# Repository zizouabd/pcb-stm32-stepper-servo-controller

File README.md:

# 🚀 Contrôleur STM32 - 2x Moteurs Pas-à-Pas (A4988) & 4x Servomoteurs

Ce dépôt contient la conception matérielle complète (schématique et PCB 2 couches $100\text{ mm} \times 100\text{ mm}$) d'une carte de contrôle embarquée pour la robotique et l'automatisme. Elle est pilotée par une **STM32 Black Pill** et alimentée par une batterie **LiPo 3S (12V)**.

---

## 📸 Aperçu du Projet

### 1. Schéma Électrique

### 2. Routage PCB (Vue 2D)

### 3. Rendu 3D de la Carte

---

## ⚡ Architecture d'Alimentation : La stratégie des "Deux Bucks"

La carte accepte une tension d'entrée principale $12\text{ V}$ via un connecteur **XT60**. Pour garantir une stabilité maximale et isoler les bruits électromécaniques, nous avons fait le choix d'intégrer **deux convertisseurs Buck (DC-DC) distincts** :

### 1. Buck 3.3V (Logique & Microcontrôleur)
* **Rôle :** Alimentation stable du STM32 (broche `VDD`) et des entrées logiques des drivers A4988.
* **Intérêt :** Consommation faible et constante. L'isolation de ce rail protège le processeur contre les chutes de tension (*brownouts*).

### 2. Buck 5V (Puissance Servomoteurs)
* **Rôle :** Alimentation directe des 4 servomoteurs (`J5` à `J8`) et du rail `VIN` de secours.
* **Intérêt :** Absorbe les forts appels de courant et le bruit inductif (*Back-EMF*) générés par les moteurs des servos sans impacter la logique numérique du STM32.

---

## 🔋 Rôle et Placement des Condensateurs de Filtrage ($220\text{ µF}$)

Pour assurer la longévité des composants et la stabilité des tensions, des condensateurs électrolytiques de **$220\text{ µF}$** ont été intégrés aux emplacements stratégiques de la carte :

### 1. Condensateurs sur la ligne `VMOT` des A4988 ($220\text{ µF}$)
Placés au plus près de la broche d'alimentation haute tension (`VMOT`) de chaque driver pas-à-pas :
* **Protection contre les surtensions inductives (Back-EMF) :** Les bobines des moteurs pas-à-pas génèrent de violents pics de tension en retour lors des commutations rapides ou du freinage. Sans ces condensateurs de $220\text{ µF}$, ces transitoires peuvent dépasser la tension maximale tolérée par le A4988 ($35\text{ V}$) et détruire instantanément le driver.
* **Réservoir d'énergie local :** Ils fournissent l'énergie instantanée nécessaire au hachage PWM du courant dans les phases des moteurs, évitant que les pics de courant ne se propagent sur toute la ligne $12\text{ V}$.

### 2. Condensateur en sortie du Buck 5V ($220\text{ µF}$)
Placé immédiatement en sortie du convertisseur $5\text{ V}$ alimentant les servomoteurs :
* **Absorption des pics de démarrage (Inrush Current) :** Un servomoteur peut appeler plusieurs ampères pendant quelques millisecondes lorsqu'il démarre ou change brutalement de sens. Ce condensateur de $220\text{ µF}$ sert de réservoir d'énergie immédiat pour lisser ces appels de courant et éviter l'écroulement de la ligne $5\text{ V}$.
* **Filtrage de l'ondulation (Ripple) :** Il réduit le bruit haute fréquence issu du hachage interne du Buck $5\text{ V}$, garantissant un signal propre pour les servos et l'électronique annexe.

---

## 📐 Création des Empreintes Personnalisées (Custom Footprints)

Afin d'assurer un assemblage parfait et de respecter les dimensions compactes de la carte ($100\text{ mm} \times 100\text{ mm}$), plusieurs empreintes spécifiques ont été créées sur mesure dans une bibliothèque dédiée du projet (`.pretty`) :

* **Modules Buck DC-DC (`buck3.3V1` & `buck5V1`) :** Les modules abaisseurs génériques ne possédant pas de standard de perçage universel, leurs empreintes ont été modélisées manuellement (espacement exact des broches `IN+`, `IN-`, `OUT+`, `OUT-` et dimensions hors-tout) pour s'intégrer directement comme cartes filles.
* **STM32 Black Pill (`Black_Pill_v3.1`) :** Empreinte personnalisée assurant le pitch standard de $2.54\text{ mm}$ entre les rangées de broches et l'intégration exacte du connecteur USB-C.

---

## 🛠️ Contraintes de Fabrication & Règles de Routage (DRC)

Le routage de la carte a été validé sous KiCad avec zéro erreur DRC selon les règles de fabrication industrielles standard :

| Paramètre | Valeur Minimale Validée |
| :--- | :--- |
| **Largeur des pistes de signal** (`STEP`, `DIR`, `SERVO`) | `0.3 mm`  |
| **Largeur des pistes de puissance** (`+5V`, `+12V`, Moteurs) | `0.8 mm` à `2.5 mm` |
| **Isolement entre pistes (Clearance)** | `0.3 mm` |
| **Distance cuivre au bord de carte (Edge.Cuts)** | `0.5 mm` |
| **Plan de masse** | Plan continu sur couche inférieure (`B.Cu`) |

---

## ⚠️ Note Importante : Configuration de la broche PA15 (SWD)

Sur cette carte, la broche **`PA15`** du STM32 est reliée au signal `MS2` du premier driver A4988.

* **Mode de programmation :** Par défaut, `PA15` est réservée à la fonction de débogage JTAG. Pour l'utiliser comme une broche d'entrée/sortie classique (GPIO), la programmation du STM32 **doit impérativement être effectuée en mode SWD (Serial Wire Debug)** via ST-Link (`SWDIO` sur PA13, `SWCLK` sur PA14).

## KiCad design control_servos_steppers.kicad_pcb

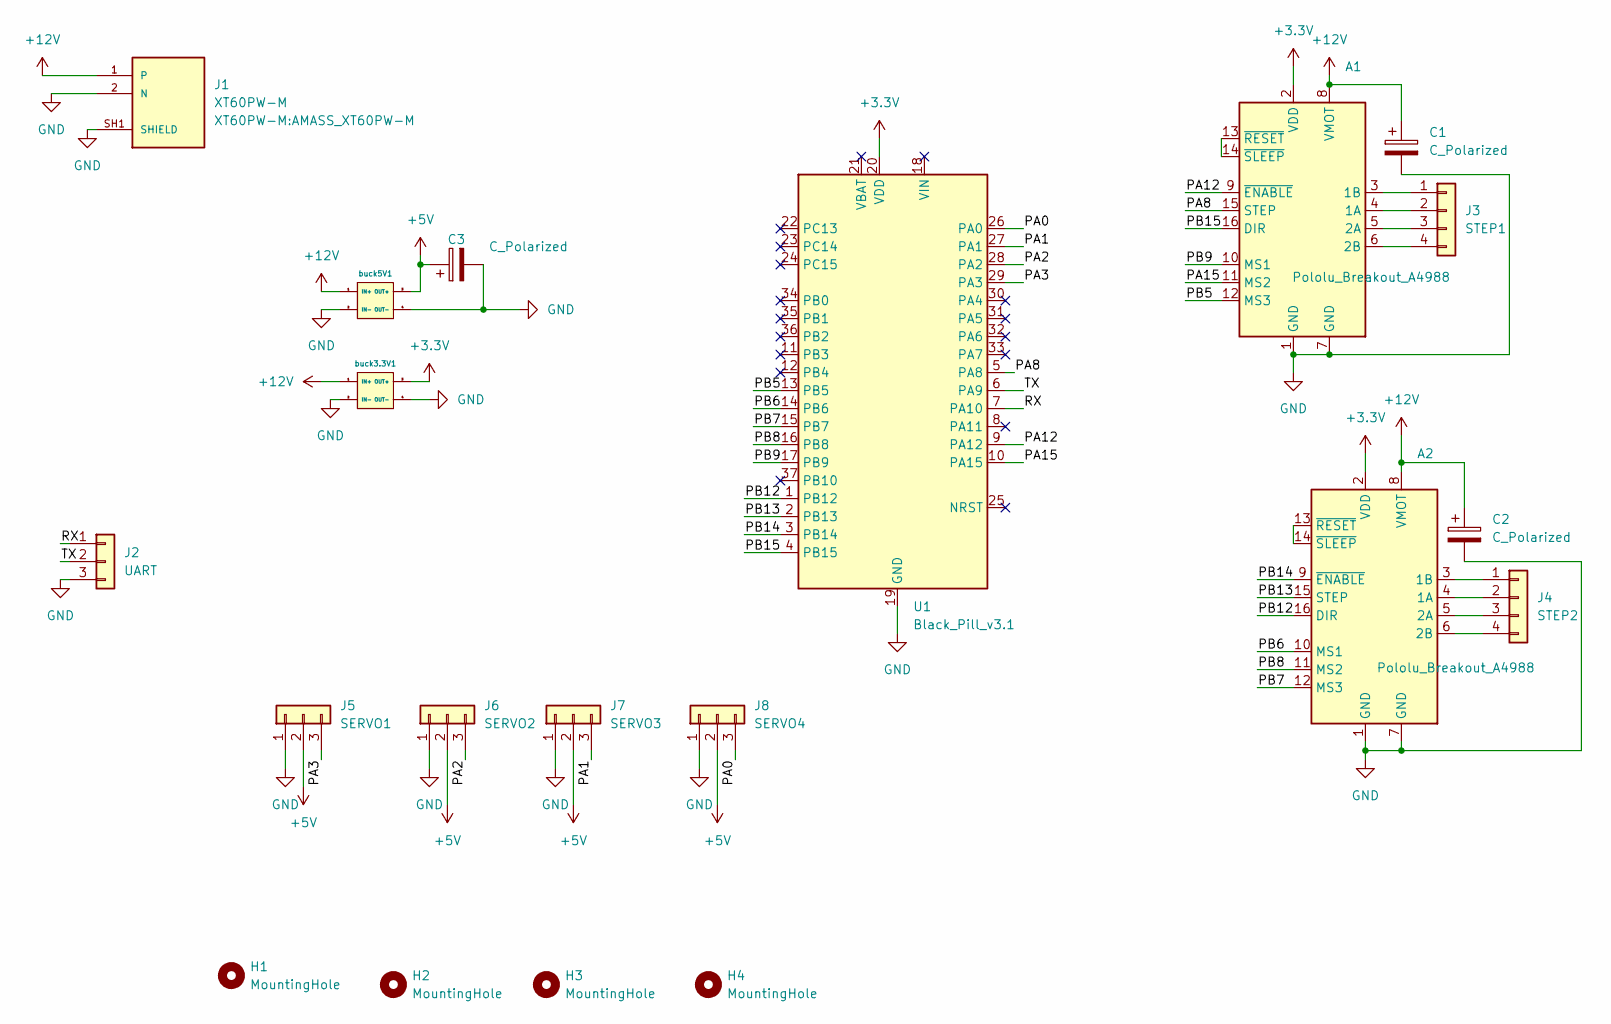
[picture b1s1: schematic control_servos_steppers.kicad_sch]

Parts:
A1, A2: Pololu_Breakout_A4988; Pololu_Breakout-16_15.2x20.3mm
C1, C2, C3: C_Polarized; CP_Radial_D8.0mm_P3.50mm
H1, H2, H3, H4: MountingHole; MountingHole_4.3mm_M4
J1: XT60PW-M; AMASS_XT60PW-M; PARTREV 1.2
J2: UART; PinHeader_1x03_P2.54mm_Vertical
J3: STEP1; PinHeader_1x04_P2.54mm_Vertical
J4: STEP2; PinHeader_1x04_P2.54mm_Vertical
J5: SERVO1; PinHeader_1x03_P2.54mm_Vertical
J6: SERVO2; PinHeader_1x03_P2.54mm_Vertical
J7: SERVO3; PinHeader_1x03_P2.54mm_Vertical
J8: SERVO4; PinHeader_1x03_P2.54mm_Vertical
U1: Black_Pill_v3.1
buck3.3V1, buck5V1: XL4015 buck module

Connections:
+3.3V: A1.2 (VDD), A2.2 (VDD), U1.20 (VDD), U1.38 (VDD), buck3.3V1.3 (OUT+)
+5V: C3.1, J5.2, J6.2, J7.2, J8.2, buck5V1.3 (OUT+)
+12V: A1.8 (VMOT), A2.8 (VMOT), C1.1, C2.1, J1.1, buck3.3V1.1 (IN+), buck5V1.1 (IN+)
/PA0: J8.3, U1.26 (PA0)
/PA1: J7.3, U1.27 (PA1)
/PA2: J6.3, U1.28 (PA2)
/PA3: J5.3, U1.29 (PA3)
/PA8: A1.15 (STEP), U1.5 (PA8)
/PA12: A1.9 (~ENABLE), U1.9 (PA12)
/PA15: A1.11 (MS2), U1.10 (PA15)
/PB5: A1.12 (MS3), U1.13 (PB5)
/PB6: A2.10 (MS1), U1.14 (PB6)
/PB7: A2.12 (MS3), U1.15 (PB7)
/PB8: A2.11 (MS2), U1.16 (PB8)
/PB9: A1.10 (MS1), U1.17 (PB9)
/PB12: A2.16 (DIR), U1.1 (PB12)
/PB13: A2.15 (STEP), U1.2 (PB13)
/PB14: A2.9 (~ENABLE), U1.3 (PB14)
/PB15: A1.16 (DIR), U1.4 (PB15)
/RX: J2.1, U1.7 (PA10)
/TX: J2.2, U1.6 (PA9)
GND: A1.1 (GND), A1.7 (GND), A2.1 (GND), A2.7 (GND), C1.2, C2.2, C3.2, J1.2 (N), J1.SH1 (SHIELD), J1.SH2 (SHIELD), J2.3, J5.1, J6.1, J7.1, J8.1, U1.19 (GND), U1.39 (GND), buck3.3V1.2 (IN-), buck3.3V1.4 (OUT-), buck5V1.2 (IN-), buck5V1.4 (OUT-)
unnamed: A1.4 (1A), J3.2
unnamed: A1.3 (1B), J3.1
unnamed: A1.5 (2A), J3.3
unnamed: A1.6 (2B), J3.4
unnamed: A1.13 (~RESET), A1.14 (~SLEEP)
unnamed: A2.4 (1A), J4.2
unnamed: A2.3 (1B), J4.1
unnamed: A2.5 (2A), J4.3
unnamed: A2.6 (2B), J4.4
unnamed: A2.13 (~RESET), A2.14 (~SLEEP)

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
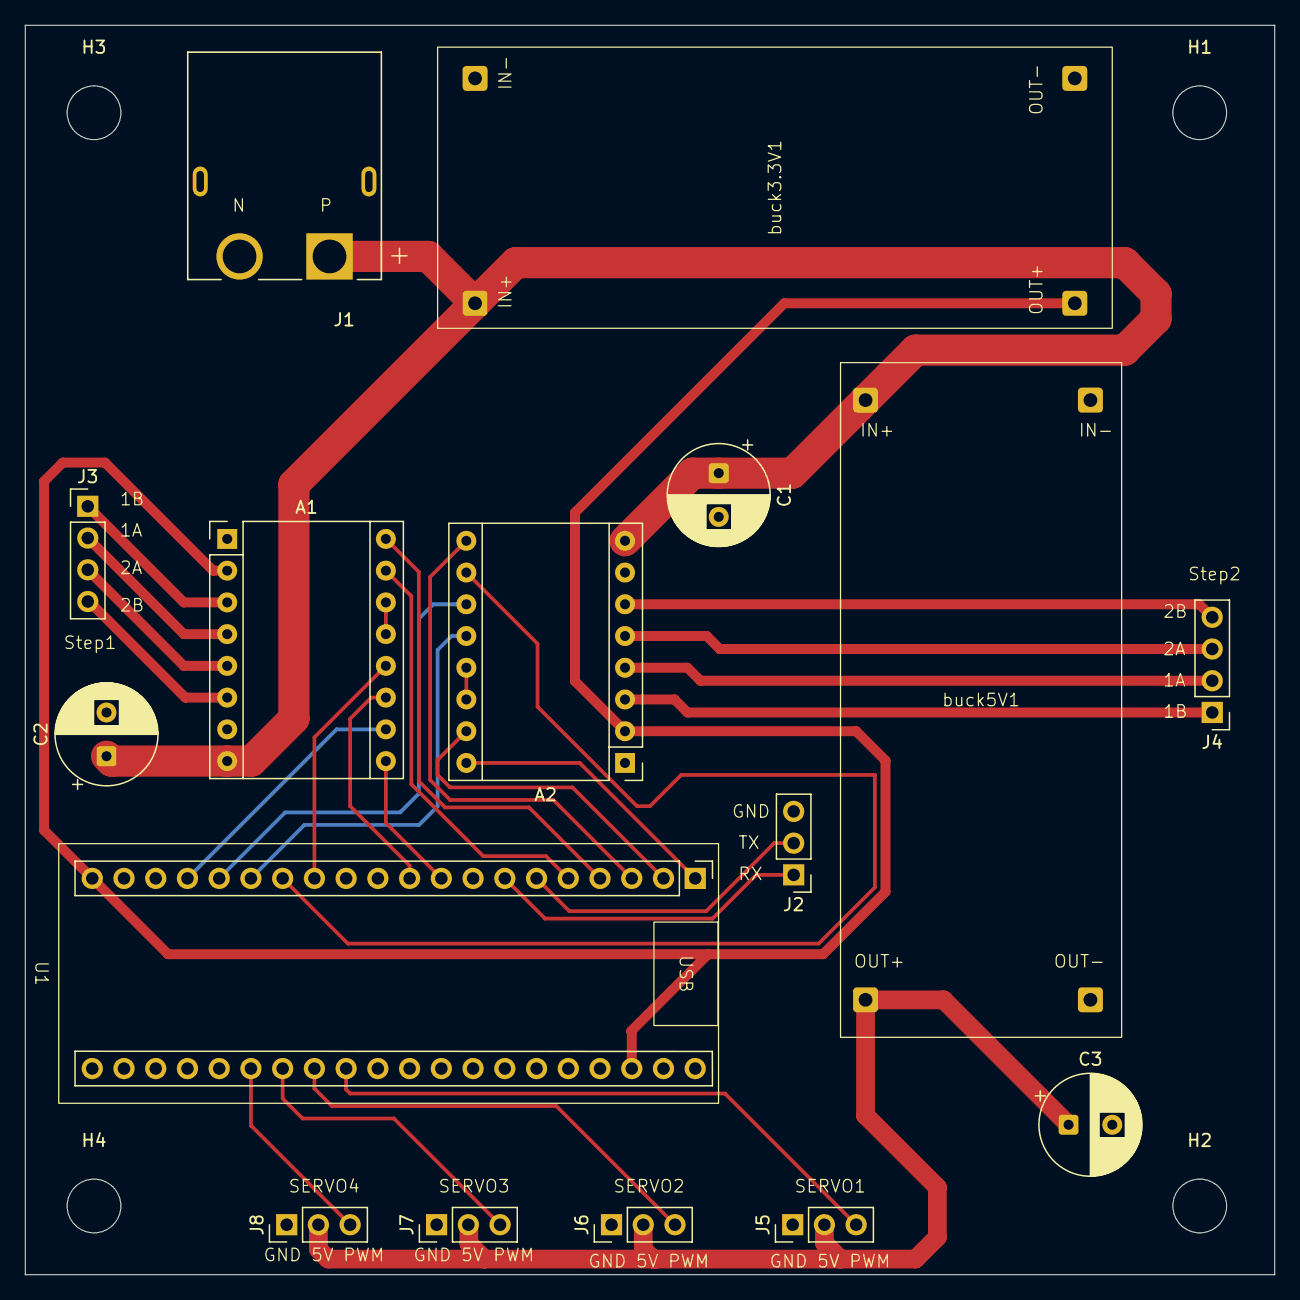
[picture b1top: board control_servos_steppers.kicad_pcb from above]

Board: 2 copper layers, 100.0 x 100.0 mm, 20 parts (0 on the bottom side), 32 nets.
